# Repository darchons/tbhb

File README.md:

tbhb
====

Tinderbox Health Bar

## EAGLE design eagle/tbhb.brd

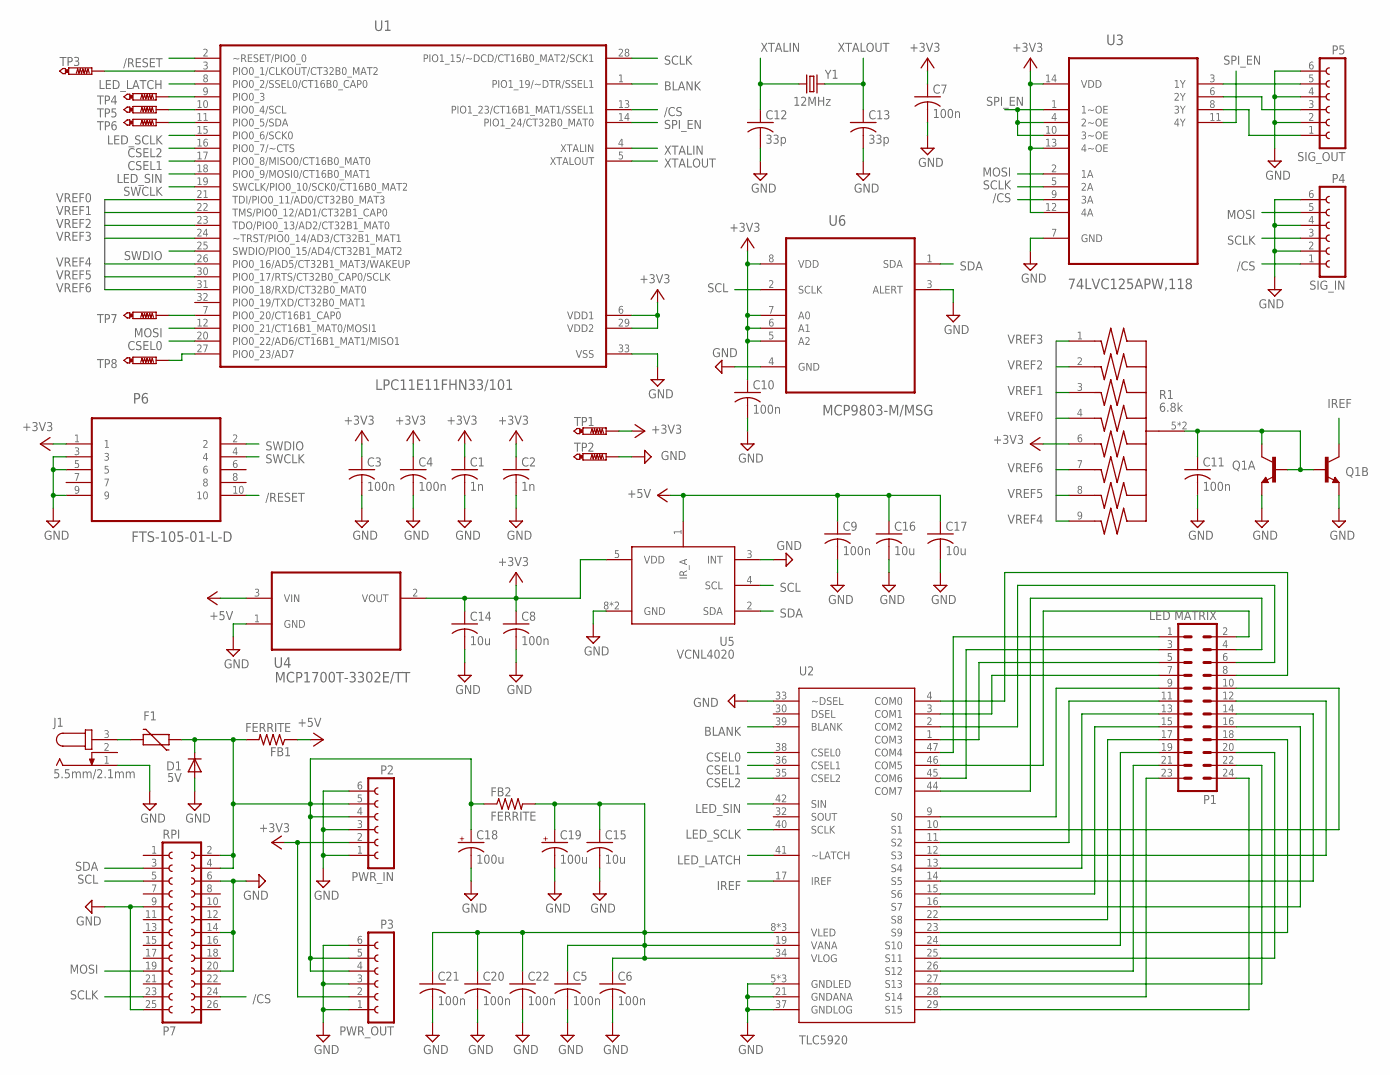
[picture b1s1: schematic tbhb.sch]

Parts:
C1, C2: 1n; C0603
C3, C4, C5, C6, C7, C8, C9, C10, C11, C20, C21, C22: 100n; C0603
C12, C13: 33p; C0603
C14, C15, C16, C17: 10u; C0805
C18, C19: 100u; CT6032; PARTNUMBER TR3C107K010C0200
D1: 5V; SOD123
F1: 2A; CT/CN1812
FB1, FB2: FERRITE; R0603
J1: 5.5mm/2.1mm; SPC4077-1
P1: LED MATRIX; MA12-2
P2: PWR_IN; FE06
P3: PWR_OUT; FE06
P4: SIG_IN; FE06
P5: SIG_OUT; FE06
P6: FTS-105-01-L-D; SAMTEC_FTS-105-01-L-D
P7: RPI; FE13-2
Q1: CMLT5088E; SOT563
R1: 6.8k; EXBD10C
TP1, TP2, TP3, TP4, TP5, TP6, TP7, TP8: PTR1TP15R; TP15R
U1: LPC11E11FHN33/101; QFN65P700X700X100-33N
U2: TLC5920; SOP63P1035X279-48N
U3: 74LVC125APW,118; SOP65P640X110-14N
U4: MCP1700T-3302E/TT; SOT95P237X112-3N
U5: VCNL4020
U6: MCP9803-M/MSG; SOP65P490X110-8N
Y1: 12MHz; CRYSTAL-50X32

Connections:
+3V3: C1.1, C2.1, C3.1, C4.1, C7.1, C8.1, C10.1, C14.1, P2.2, P3.2, P6.1, R1.6 (5), TP1.TP, U1.6 (VDD1), U1.29 (VDD2), U3.12 (4A), U3.13 (4~OE), U3.14 (VDD), U4.2 (VOUT), U5.5 (VDD), U6.5 (A2), U6.6 (A1), U6.7 (A0), U6.8 (VDD)
+5V: C9.1, C16.1, C17.1, FB1.1, U4.3 (VIN), U5.1 (IR_A)
/CS: P4.1, P7.24, U1.13 (PIO1_23/CT16B1_MAT1/SSEL1), U3.9 (3A)
/RESET: P6.10, U1.2 (~RESET/PIO0_0)
BLANK: U1.1 (PIO1_19/~DTR/SSEL1), U2.39 (BLANK)
CSEL0: U1.20 (PIO0_22/AD6/CT16B1_MAT1/MISO1), U2.38 (CSEL0)
CSEL1: U1.17 (PIO0_8/MISO0/CT16B0_MAT0), U2.36 (CSEL1)
CSEL2: U1.16 (PIO0_7/~CTS), U2.35 (CSEL2)
GND: C1.2, C2.2, C3.2, C4.2, C5.2, C6.2, C7.2, C8.2, C9.2, C10.2, C11.2, C12.2, C13.2, C14.2, C15.2, C16.2, C17.2, C18.-, C19.-, C20.2, C21.2, C22.2, D1.A, J1.1, P2.1, P2.3, P2.6, P3.1, P3.3, P3.6, P4.2, P4.4, P4.6, P5.2, P5.4, P5.6, P6.3, P6.5, P6.9, P7.6, P7.9, P7.14, P7.20, P7.25, Q1.1 (E), Q1.4 (E), TP2.TP, U1.33 (VSS), U2.5 (GNDLED), U2.21 (GNDANA), U2.33 (~DSEL), U2.37 (GNDLOG), U2.43 (GNDLED), U2.48 (GNDLED), U3.7 (GND), U4.1 (GND), U5.3 (INT), U5.8 (GND), U5.9 (GND), U6.3 (ALERT), U6.4 (GND)
IREF: Q1.3 (C), U2.17 (IREF)
LED_LATCH: U1.8 (PIO0_2/SSEL0/CT16B0_CAP0), U2.41 (~LATCH)
LED_SCLK: U1.15 (PIO0_6/SCK0), U2.40 (SCLK)
LED_SIN: U1.18 (PIO0_9/MOSI0/CT16B0_MAT1), U2.42 (SIN)
MOSI: P4.5, P7.19, U1.12 (PIO0_21/CT16B1_MAT0/MOSI1), U3.2 (1A)
unnamed: TP3.TP, U1.3 (PIO0_1/CLKOUT/CT32B0_MAT2)
unnamed: C18.+, D1.C, F1.1, FB1.2, FB2.1, P2.4, P2.5, P3.4, P3.5, P7.2, P7.4
unnamed: P1.1, U2.47 (COM4)
unnamed: P1.3, U2.45 (COM6)
unnamed: P1.5, U2.1 (COM3)
unnamed: P1.7, U2.3 (COM1)
unnamed: P1.8, U2.4 (COM0)
unnamed: P1.6, U2.2 (COM2)
unnamed: P1.4, U2.44 (COM7)
unnamed: P1.2, U2.46 (COM5)
unnamed: P1.9, U2.9 (S0)
unnamed: P1.11, U2.11 (S2)
unnamed: TP5.TP, U1.10 (PIO0_4/SCL)
unnamed: TP4.TP, U1.9 (PIO0_3)
unnamed: P1.23, U2.28 (S14)
unnamed: P1.24, U2.29 (S15)
unnamed: P1.12, U2.12 (S3)
unnamed: P1.22, U2.27 (S13)
unnamed: P1.21, U2.26 (S12)
unnamed: P1.19, U2.24 (S10)
unnamed: P5.1, U3.8 (3Y)
unnamed: P5.3, U3.6 (2Y)
unnamed: P5.5, U3.3 (1Y)
unnamed: C11.1, Q1.2 (B), Q1.5 (B), Q1.6 (C), R1.5 (C), R1.10 (C)
unnamed: F1.2, J1.3
unnamed: TP6.TP, U1.11 (PIO0_5/SDA)
unnamed: TP8.TP, U1.27 (PIO0_23/AD7)
unnamed: P1.20, U2.25 (S11)
unnamed: TP7.TP, U1.7 (PIO0_20/CT16B1_CAP0)
unnamed: P1.17, U2.22 (S8)
unnamed: P1.13, U2.13 (S4)
unnamed: P1.10, U2.10 (S1)
unnamed: P1.18, U2.23 (S9)
unnamed: P1.15, U2.15 (S6)
unnamed: P1.16, U2.16 (S7)
unnamed: P1.14, U2.14 (S5)
SCL: P7.5, U5.4 (SCL), U6.2 (SCLK)
SCLK: P4.3, P7.23, U1.28 (PIO1_15/~DCD/CT16B0_MAT2/SCK1), U3.5 (2A)
SDA: P7.3, U5.2 (SDA), U6.1 (SDA)
SPI_EN: U1.14 (PIO1_24/CT32B0_MAT0), U3.1 (1~OE), U3.4 (2~OE), U3.10 (3~OE), U3.11 (4Y)
SWCLK: P6.4, U1.19 (SWCLK/PIO0_10/SCK0/CT16B0_MAT2)
SWDIO: P6.2, U1.25 (SWDIO/PIO0_15/AD4/CT32B1_MAT2)
VLED: C5.1, C6.1, C15.1, C19.+, C20.1, C21.1, C22.1, FB2.2, U2.8 (VLED), U2.18 (VLED), U2.19 (VANA), U2.31 (VLED), U2.34 (VLOG)
VREF0: R1.4, U1.21 (TDI/PIO0_11/AD0/CT32B0_MAT3)
VREF1: R1.3, U1.22 (TMS/PIO0_12/AD1/CT32B1_CAP0)
VREF2: R1.2, U1.23 (TDO/PIO0_13/AD2/CT32B1_MAT0)
VREF3: R1.1, U1.24 (~TRST/PIO0_14/AD3/CT32B1_MAT1)
VREF4: R1.9 (8), U1.26 (PIO0_16/AD5/CT32B1_MAT3/WAKEUP)
VREF5: R1.8 (7), U1.30 (PIO0_17/RTS/CT32B0_CAP0/SCLK)
VREF6: R1.7 (6), U1.31 (PIO0_18/RXD/CT32B0_MAT0)
XTALIN: C12.1, U1.4 (XTALIN), Y1.1
XTALOUT: C13.1, U1.5 (XTALOUT), Y1.2

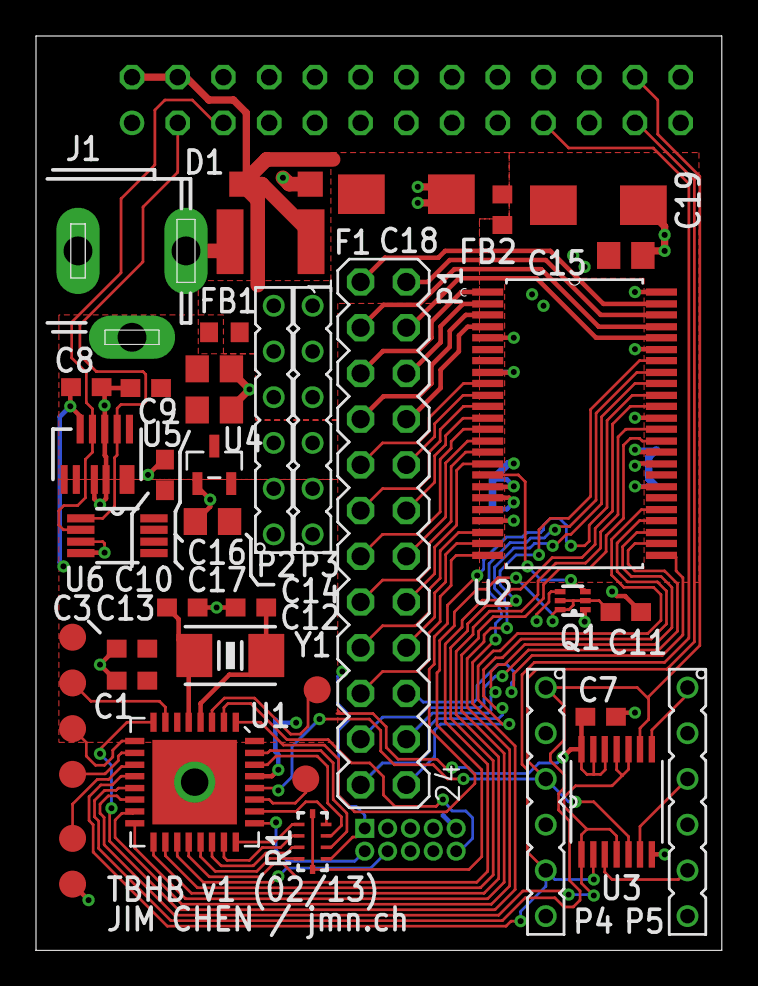
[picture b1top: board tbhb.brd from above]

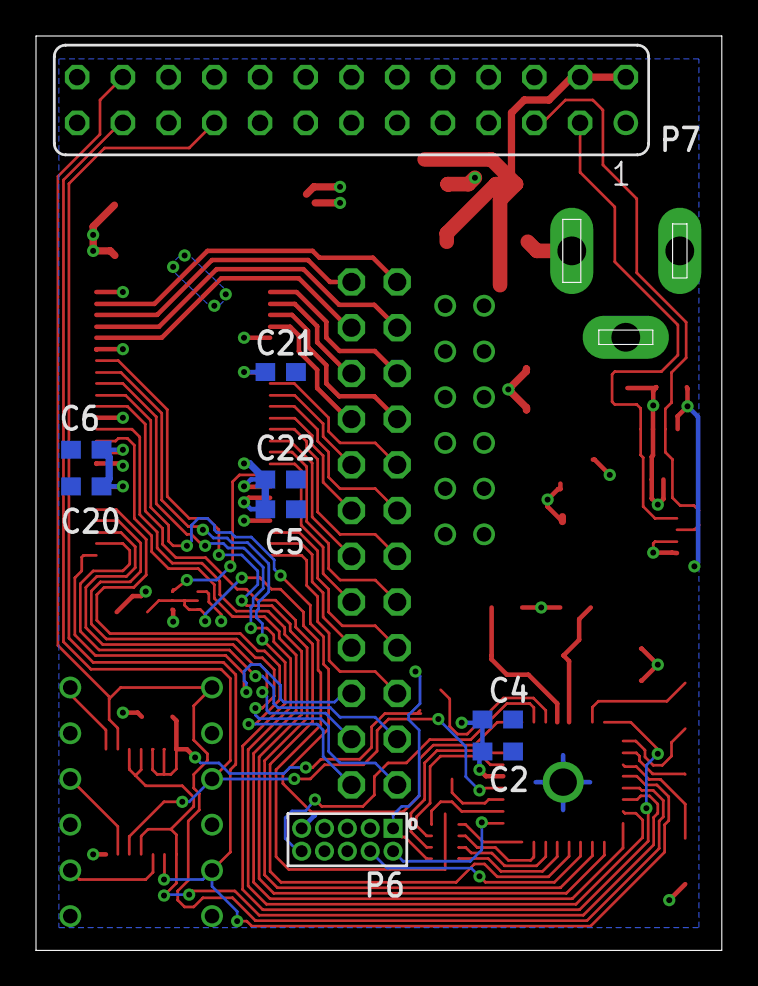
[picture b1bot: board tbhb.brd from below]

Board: 2 copper layers, 38.1 x 50.8 mm, 51 parts (9 on the bottom side), 66 nets.

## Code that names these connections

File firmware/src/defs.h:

/*
 * defs.h
 *
 *  Created on: Mar 15, 2013
 *      Author: nchen
 */

#ifndef DEFS_H_
#define DEFS_H_

#define ALWAYS_INLINE   __attribute__((always_inline))

// Format: 0xGGRR
typedef uint16_t    pixel_t;
// Format: 0xGGGGRRRR
typedef uint32_t    gamma_pixel_t;

// Format: 0bXXXXXXXXXXXXXXXX
//  where each X corresponds to a driver channel
typedef uint16_t    line_t;

#define BITS        9
#define CHANNELS    2   // red and green
#define WIDTH       8
#define LINES       8
#define BUFFERS     3
#define SRC_BUFFERS 2   // Lines of source to buffer

ALWAYS_INLINE
static gamma_pixel_t
CorrectGamma(pixel_t pixel) {
    uintptr_t red = (((uintptr_t)pixel) & 0xff) + 1;
    uintptr_t green = (((uintptr_t)pixel) & 0xff00) + 0x100;
    return ((((uintptr_t)(red * red) - 1) >> (16 - BITS)) |
            (((uintptr_t)(green * green) - 0x10000) >> (16 - BITS))) &
            (((1 << BITS) - 1) | ((0x10000 << BITS) - 0x10000));
}

// Size of a timer program for one line
#define PROGRAM_SIZE    (((BITS - 1) * BITS) + 1)

// Size of program to generate per received pixel, excluding first program
//  program entry and final received pixel in a line (see SetFrameData)
#define PROGRAM_STEP    (((PROGRAM_SIZE - 1) + (WIDTH - 2)) / (WIDTH - 1))

#if (BUFFERS & (BUFFERS - 1)) == 0
#define ROUND_BUFFER_INDEX(i)   ((i) & (BUFFERS - 1))
#else
#define ROUND_BUFFER_INDEX(i)   ((i) >= BUFFERS ? (i) - BUFFERS : (i))
#endif

static const intptr_t LINE_SEQUENCE[LINES + 1] = {4, 6, 3, 1, 0, 2, 7, 5, 4};

#define HOST_SPI_CLK    4000000
#define DRIVER_SPI_CLK  12000000
#define DRIVER_LINE_CLK 600000

#define NVIC_PRIO_DRIVER_TIMER  0
#define NVIC_PRIO_HOST_SSP      3

#define MAKE_PIO_(prefix, port, pin)    prefix ## PIO ## port ## _ ## pin
#define MAKE_PIO(prefix, port, pin)     MAKE_PIO_(prefix, port, pin)

// /EN      pin 14 (PIO1_24/CT32B0_MAT0)
#define SPI_EN_PORT 1
#define SPI_EN_PIN  24
#define SPI_EN_PIO  MAKE_PIO(, SPI_EN_PORT, SPI_EN_PIN)
// MOSI     pin 12 (PIO0_21/CT16B1_MAT0/MOSI1)
#define MOSI_PORT   0
#define MOSI_PIN    21
#define MOSI_PIO    MAKE_PIO(, MOSI_PORT, MOSI_PIN)
// SCLK     pin 28 (PIO1_15/DCD/CT16B0_MAT2/SCK1)
#define SCLK_PORT   1
#define SCLK_PIN    15
#define SCLK_PIO    MAKE_PIO(, SCLK_PORT, SCLK_PIN)
// /CS      pin 13 (PIO1_23/CT16B1_MAT1/SSEL1)
#define CS_PORT     1
#define CS_PIN      23
#define CS_PIO      MAKE_PIO(, CS_PORT, CS_PIN)

// MOSI     pin 18 (PIO0_9/MOSI0/CT16B0_MAT1)
#define LED_SIN_PORT    0
#define LED_SIN_PIN     9
#define LED_SIN_PIO     MAKE_PIO(, LED_SIN_PORT, LED_SIN_PIN)
// SCLK     pin 15 (PIO0_6/SCK0)
#define LED_SCLK_PORT   0
#define LED_SCLK_PIN    6
#define LED_SCLK_PIO    MAKE_PIO(, LED_SCLK_PORT, LED_SCLK_PIN)
// /CS      pin 8 (PIO0_2/SSEL0/CT16B0_CAP0)
#define LED_LATCH_PORT  0
#define LED_LATCH_PIN   2
#define LED_LATCH_PIO   MAKE_PIO(, LED_LATCH_PORT, LED_LATCH_PIN)

// VREF0    pin 21 (TDI/PIO0_11/AD0/CT32B0_MAT3)
#define VREF0_PORT  0
#define VREF0_PIN   11
#define VREF0_PIO   MAKE_PIO(TDI_, VREF0_PORT, VREF0_PIN)
// VREF1    pin 22 (TMS/PIO0_12/AD1/CT32B1_CAP0)
#define VREF1_PORT  0
#define VREF1_PIN   12
#define VREF1_PIO   MAKE_PIO(TMS_, VREF1_PORT, VREF1_PIN)
// VREF2    pin 23 (TDO/PIO0_13/AD2/CT32B1_MAT0)
#define VREF2_PORT  0
#define VREF2_PIN   13
#define VREF2_PIO   MAKE_PIO(TDO_, VREF2_PORT, VREF2_PIN)
// VREF3    pin 24 (TRST/PIO0_14/AD3/CT32B1_MAT1)
#define VREF3_PORT  0
#define VREF3_PIN   14
#define VREF3_PIO   MAKE_PIO(TRST_, VREF3_PORT, VREF3_PIN)
// VREF4    pin 26 (PIO0_16/AD5/CT32B1_MAT3/WAKEUP)
#define VREF4_PORT  0
#define VREF4_PIN   16
#define VREF4_PIO   MAKE_PIO(, VREF4_PORT, VREF4_PIN)
// VREF5    pin 30 (PIO0_17/RTS/CT32B0_CAP0/SCLK)
#define VREF5_PORT  0
#define VREF5_PIN   17
#define VREF5_PIO   MAKE_PIO(, VREF5_PORT, VREF5_PIN)
// VREF6    pin 31 (PIO0_18/RXD/CT32B0_MAT0)
#define VREF6_PORT  0
#define VREF6_PIN   18
#define VREF6_PIO   MAKE_PIO(, VREF6_PORT, VREF6_PIN)

#define VREF_SIZE   7

static const uintptr_t IREF_DIR[] = { 0b11111111, 0b10001111, 0b10000111,
        0b10000011, 0b11111111, 0b10000001, 0b11011111, 0b10000000, 0b11001111,
        0b11000111, 0b11000011, 0b11000001, 0b11111111, 0b11000000, 0b11101111,
        0b11100111, 0b11100011, 0b11100001, 0b11100000, 0b11111111, 0b11110111,
        0b11110011, 0b11110001, 0b11110000, 0b11111111, 0b11111011, 0b11111001,
        0b11111000, 0b11111111, 0b11111101, 0b11111100, 0b11111111 };
static const uintptr_t IREF_OUT[] = { 0b10000000, 0b10000000, 0b10000000,
        0b10000000, 0b11000000, 0b10000000, 0b11000000, 0b10000000, 0b11000000,
        0b11000000, 0b11000000, 0b11000000, 0b11100000, 0b11000000, 0b11100000,
        0b11100000, 0b11100000, 0b11100000, 0b11100000, 0b11110000, 0b11110000,
        0b11110000, 0b11110000, 0b11110000, 0b11111000, 0b11111000, 0b11111000,
        0b11111000, 0b11111100, 0b11111100, 0b11111100, 0b11111110 };

// Dummy arrays to detect mismatch in size between IREF_DIR and IREF_OUT
static const uintptr_t IREF_DUMMY1[sizeof(IREF_DIR) - sizeof(IREF_OUT)];
static const uintptr_t IREF_DUMMY2[sizeof(IREF_OUT) - sizeof(IREF_DIR)];

#define IREF_LEVELS (sizeof(IREF_DIR) / sizeof(IREF_DIR[0]))

// CSEL0    pin 20 (PIO0_22/AD6/CT16B1_MAT1/MISO1)
#define CSEL0_PORT  0
#define CSEL0_PIN   22
#define CSEL0_PIO   MAKE_PIO(, CSEL0_PORT, CSEL0_PIN)
// CSEL1    pin 17 (PIO0_8/MISO0/CT16B0_MAT0)
#define CSEL1_PORT  0
#define CSEL1_PIN   8
#define CSEL1_PIO   MAKE_PIO(, CSEL1_PORT, CSEL1_PIN)
// CSEL2    pin 16 (PIO0_7/CTS)
#define CSEL2_PORT  0
#define CSEL2_PIN   7
#define CSEL2_PIO   MAKE_PIO(, CSEL2_PORT, CSEL2_PIN)

// BLANK    pin 1 (PIO1_19/DTR/SSEL1)
#define BLANK_PORT  1
#define BLANK_PIN   19
#define BLANK_PIO   MAKE_PIO(, BLANK_PORT, BLANK_PIN)

#endif /* DEFS_H_ */

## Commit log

2013-04-26 Initial files
2013-04-26 Make spidev work
2013-04-26 Fix firmware logic and line ending
2016-01-04 General fixes
